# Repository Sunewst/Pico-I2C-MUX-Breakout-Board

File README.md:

<div align="center">

## Raspberry Pi Pico/W Breakout MUX Board

This PCB designed in KiCAD allows a Raspberry Pi Pico W, or normal version, to communicate with 8 I2C devices that have matching addresses. This board is based on breakout muiltiplexers sold by [Adafruit](https://www.adafruit.com/product/5626) and [SparkFun](https://www.sparkfun.com/sparkfun-qwiic-mux-breakout-8-channel-tca9548a.html). 

This also means the licence from these muiltiplexers, Creative Commons, applies to this one aswell.

</div>

---

## Arduino and CircuitPython
This breakout board works with either Arduino or CircuitPython.
> [!NOTE]
> For CircuitPython, I would recommend using the [libraries created by Adafruit for TCA9548a MUX use](https://learn.adafruit.com/adafruit-pca9548-8-channel-stemma-qt-qwiic-i2c-multiplexer/circuitpython-python).

The main connection are

SDA: GP4

SCL: GP5

MISO: GP16

MOSI: GP19

CLK: GP18

CS: GP17

Neopixel: GP6

---

## Creating and Changing this Design
1. Download the zip of this repo or clone it

2. Open the KiCAD project file.
> [!NOTE]
> This project was updated to KiCAD 9.0.

3. Examine and understand the schematic and PCB layout
> [!NOTE]
> The 3D models for the certain components might need to have their file path updated and their 3D models posistion adjusted to appear correctly on your PC.

4. Use your preferred PCB manufacture to order the PCB

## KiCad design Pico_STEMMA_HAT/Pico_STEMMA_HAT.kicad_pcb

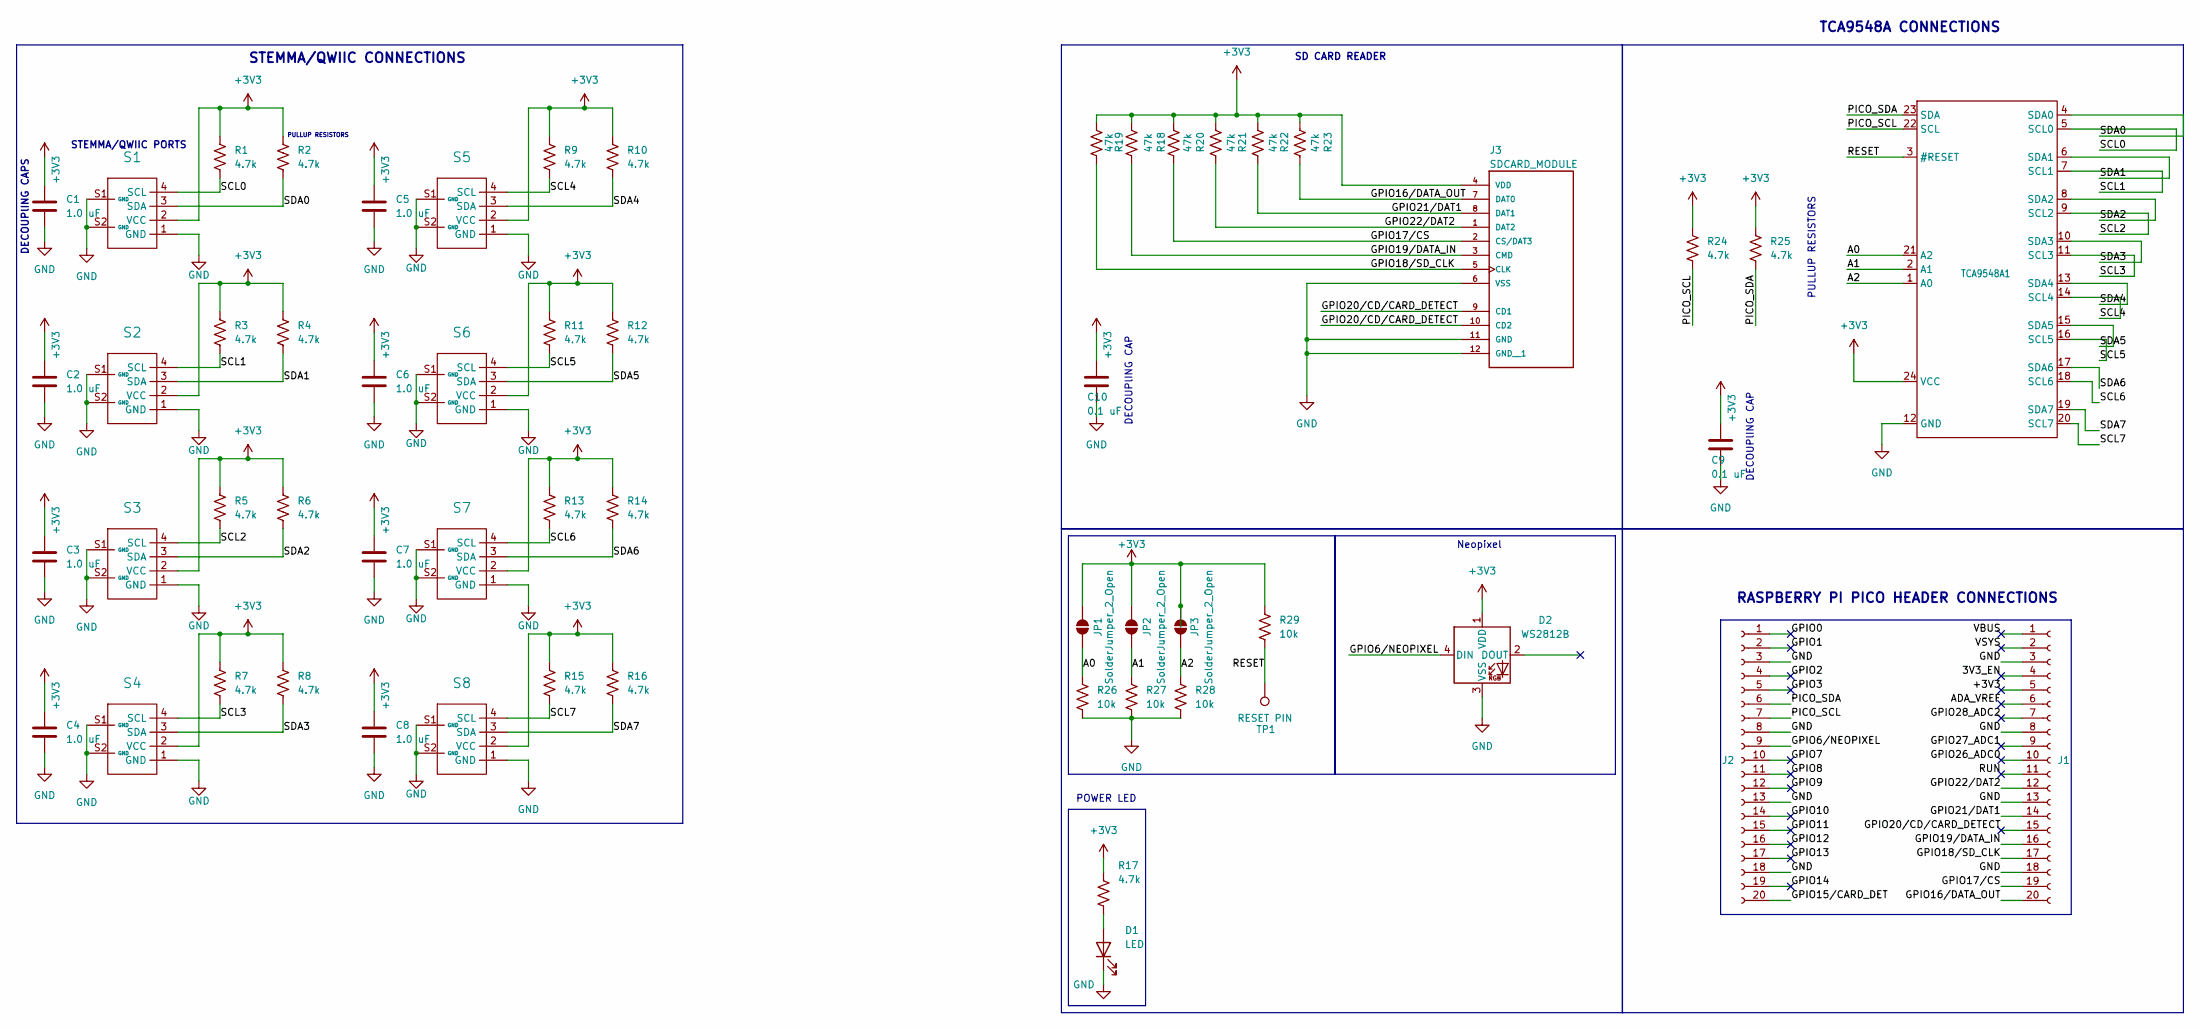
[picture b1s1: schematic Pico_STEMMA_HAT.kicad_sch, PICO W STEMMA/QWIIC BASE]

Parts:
C1, C2, C3, C4, C5, C6, C7, C8: 1.0 uF; C_0603_1608Metric
C9, C10: 0.1 uF; C_0603_1608Metric
D1: LED; LED_0603_1608Metric
D2: WS2812B; LED_WS2812B_PLCC4_5.0x5.0mm_P3.2mm
J1, J2: Conn_01x20_Socket; PinSocket_1x20_P2.54mm_Vertical
J3: SDCARD_MODULE; SDCARD_MODULE_Footprint
JP1, JP2, JP3: SolderJumper_2_Open; SolderJumper-2_P1.3mm_Open_TrianglePad1.0x1.5mm
R1, R2, R3, R4, R5, R6, R7, R8, R9, R10, R11, R12, R13, R14, R15, R16, R17, R24, R25: 4.7k; R_0603_1608Metric
R18, R19, R20, R21, R22, R23: 47k; R_0603_1608Metric
R26, R27, R28, R29: 10k; R_0603_1608Metric
S1, S2, S3, S4, S5, S6, S7, S8: STEMMAQWIIC_Footprint
TCA9548A1: TCA9548A_Footprint
TP1: RESET PIN; TestPoint_THTPad_1.0x1.0mm_Drill0.5mm

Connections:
+3V3: C1.1, C2.1, C3.1, C4.1, C5.1, C6.1, C7.1, C8.1, C9.1, C10.1, D2.1 (VDD), J1.5, J3.4 (VDD), JP1.2 (B), JP2.2 (B), JP3.2 (B), R1.1, R2.1, R3.1, R4.1, R5.1, R6.1, R7.1, R8.1, R9.1, R10.1, R11.1, R12.1, R13.1, R14.1, R15.1, R16.1, R17.1, R18.1, R19.1, R20.1, R21.1, R22.1, R23.1, R24.1, R25.1, R29.1, S1.2 (VCC), S2.2 (VCC), S3.2 (VCC), S4.2 (VCC), S5.2 (VCC), S6.2 (VCC), S7.2 (VCC), S8.2 (VCC), TCA9548A1.24 (VCC)
/3V3_EN: J1.4
/A0: JP1.1 (A), R26.1, TCA9548A1.21 (A2)
/A1: JP2.1 (A), R27.1, TCA9548A1.2 (A1)
/A2: JP3.1 (A), R28.1, TCA9548A1.1 (A0)
/ADA_VREF: J1.6
/GPIO0: J2.1
/GPIO1: J2.2
/GPIO2: J2.4
/GPIO3: J2.5
/GPIO6/NEOPIXEL: D2.4 (DIN), J2.9
/GPIO7: J2.10
/GPIO8: J2.11
/GPIO9: J2.12
/GPIO10: J2.14
/GPIO11: J2.15
/GPIO12: J2.16
/GPIO13: J2.17
/GPIO14: J2.19
/GPIO15/CARD_DET: J2.20
/GPIO16/DATA_OUT: J1.20, J3.7 (DAT0), R23.2
/GPIO17/CS: J1.19, J3.2 (CS/DAT3), R20.2
/GPIO18/SD_CLK: J1.17, J3.5 (CLK), R19.2
/GPIO19/DATA_IN: J1.16, J3.3 (CMD), R18.2
/GPIO20/CD/CARD_DETECT: J1.15, J3.9 (CD1), J3.10 (CD2)
/GPIO21/DAT1: J1.14, J3.8 (DAT1), R22.2
/GPIO22/DAT2: J1.12, J3.1 (DAT2), R21.2
/GPIO26_ADC0: J1.10
/GPIO27_ADC1: J1.9
/GPIO28_ADC2: J1.7
/PICO_SCL: J2.7, R24.2, TCA9548A1.22 (SCL)
/PICO_SDA: J2.6, R25.2, TCA9548A1.23 (SDA)
/RESET: R29.2, TCA9548A1.3 (#RESET), TP1.1
/RUN: J1.11
/SCL0: R1.2, S1.4 (SCL), TCA9548A1.5 (SCL0)
/SCL1: R3.2, S2.4 (SCL), TCA9548A1.7 (SCL1)
/SCL2: R5.2, S3.4 (SCL), TCA9548A1.9 (SCL2)
/SCL3: R7.2, S4.4 (SCL), TCA9548A1.11 (SCL3)
/SCL4: R9.2, S5.4 (SCL), TCA9548A1.14 (SCL4)
/SCL5: R11.2, S6.4 (SCL), TCA9548A1.16 (SCL5)
/SCL6: R13.2, S7.4 (SCL), TCA9548A1.18 (SCL6)
/SCL7: R15.2, S8.4 (SCL), TCA9548A1.20 (SCL7)
/SDA0: R2.2, S1.3 (SDA), TCA9548A1.4 (SDA0)
/SDA1: R4.2, S2.3 (SDA), TCA9548A1.6 (SDA1)
/SDA2: R6.2, S3.3 (SDA), TCA9548A1.8 (SDA2)
/SDA3: R8.2, S4.3 (SDA), TCA9548A1.10 (SDA3)
/SDA4: R10.2, S5.3 (SDA), TCA9548A1.13 (SDA4)
/SDA5: R12.2, S6.3 (SDA), TCA9548A1.15 (SDA5)
/SDA6: R14.2, S7.3 (SDA), TCA9548A1.17 (SDA6)
/SDA7: R16.2, S8.3 (SDA), TCA9548A1.19 (SDA7)
/VBUS: J1.1
/VSYS: J1.2
GND: C1.2, C2.2, C3.2, C4.2, C5.2, C6.2, C7.2, C8.2, C9.2, C10.2, D1.1 (K), D2.3 (VSS), J1.3, J1.8, J1.13, J1.18, J2.3, J2.8, J2.13, J2.18, J3.6 (VSS), J3.11 (GND), J3.12 (GND__1), R26.2, R27.2, R28.2, S1.1 (GND), S1.S1 (GND), S1.S2 (GND), S2.1 (GND), S2.S1 (GND), S2.S2 (GND), S3.1 (GND), S3.S1 (GND), S3.S2 (GND), S4.1 (GND), S4.S1 (GND), S4.S2 (GND), S5.1 (GND), S5.S1 (GND), S5.S2 (GND), S6.1 (GND), S6.S1 (GND), S6.S2 (GND), S7.1 (GND), S7.S1 (GND), S7.S2 (GND), S8.1 (GND), S8.S1 (GND), S8.S2 (GND), TCA9548A1.12 (GND)
unnamed: D1.2 (A), R17.2

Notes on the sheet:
STEMMA/QWIIC PORTS
SD CARD READER
RASPBERRY PI PICO HEADER CONNECTIONS
DECOUPlING CAP
TCA9548A CONNECTIONS
PULLUP RESISTORS
DECOUPlING CAPS
STEMMA/QWIIC CONNECTIONS
POWER LED
Neopixel

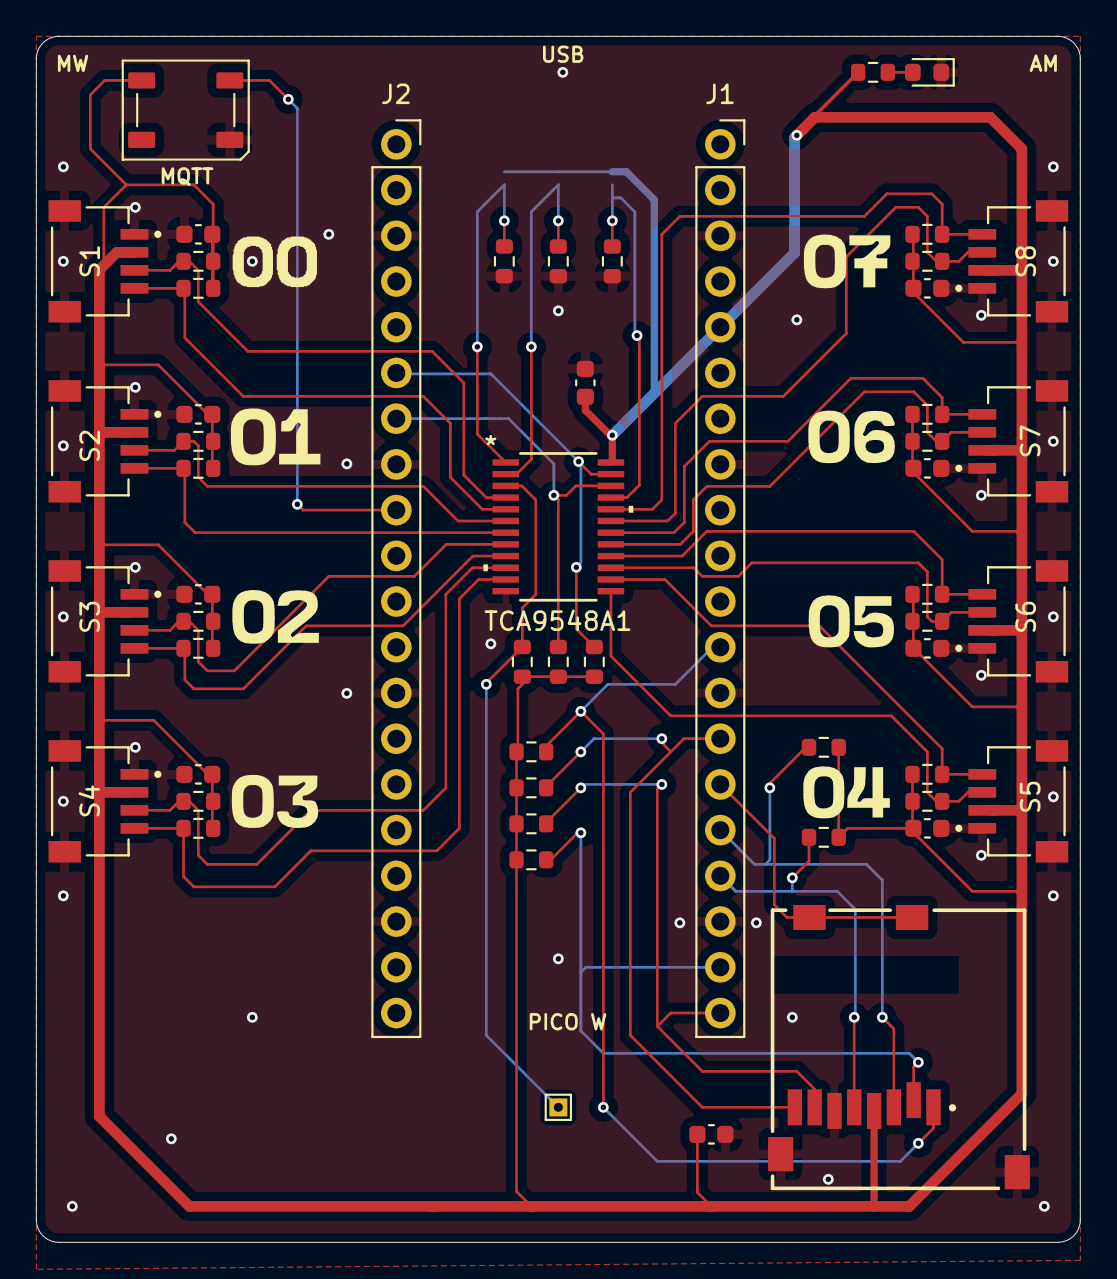
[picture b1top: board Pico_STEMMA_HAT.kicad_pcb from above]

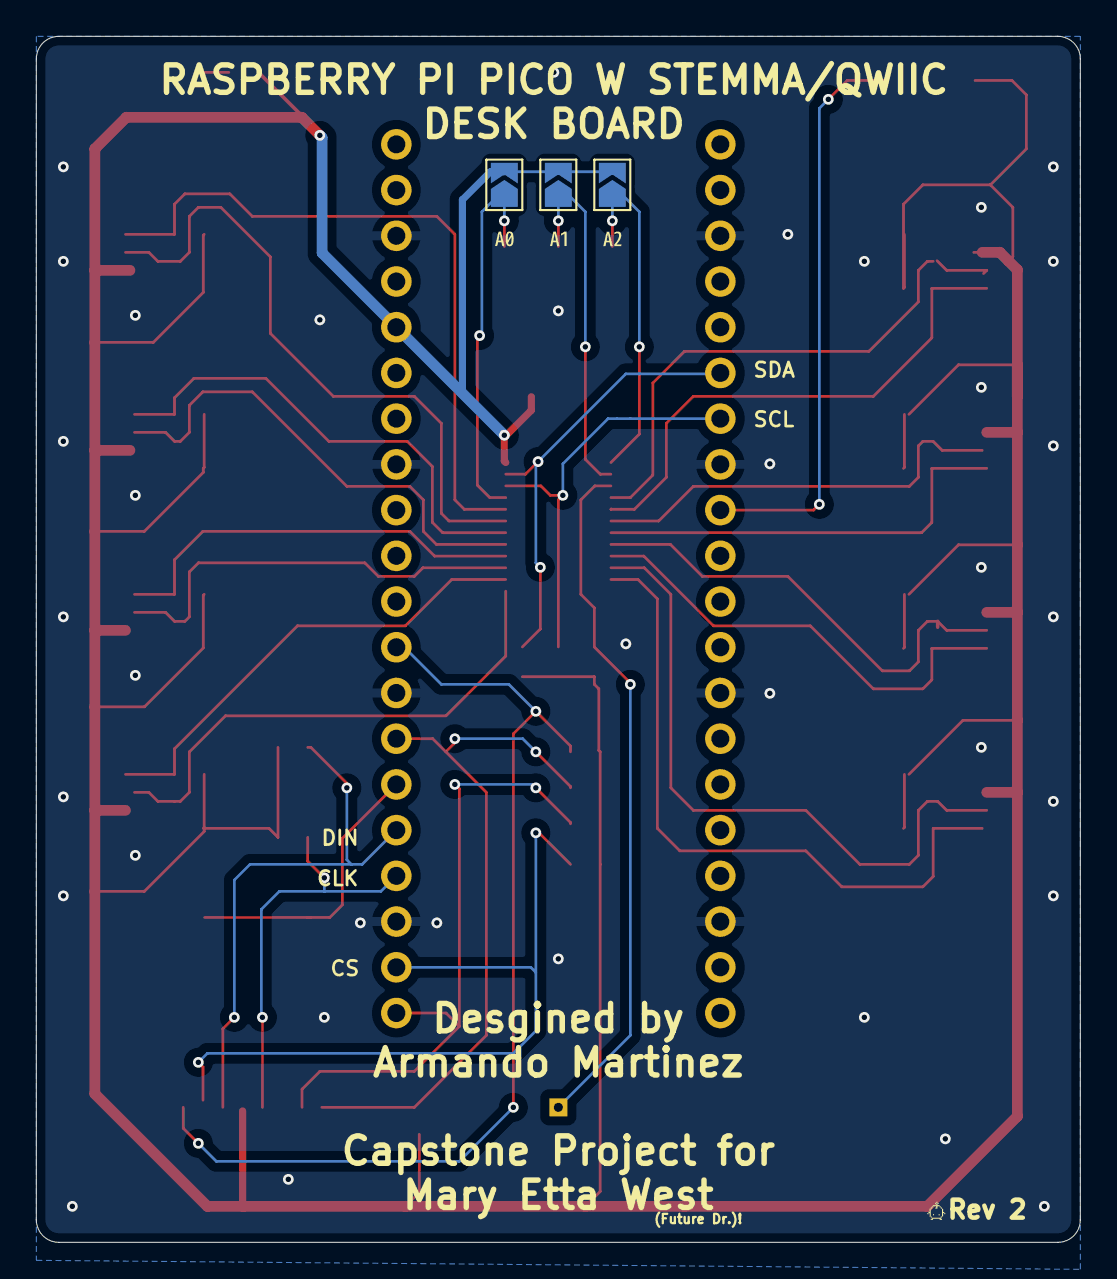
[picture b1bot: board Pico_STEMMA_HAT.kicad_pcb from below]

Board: 2 copper layers, 58.0 x 67.0 mm, 60 parts (6 on the bottom side), 33 nets.

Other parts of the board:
kibuzzard-67A6AC81: G***; kibuzzard-67A6AC81
kibuzzard-67A6B903: G***; kibuzzard-67A6B903
kibuzzard-67A6E024: G***; kibuzzard-67A6E024

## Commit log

2024-12-24 Update README.md to include the new project name
2025-01-05 Add Winter Break Progress
    Progress so far from learning KiCAD and creating the Pico W base over break. The SD card and coin battery will be added tomorrow when I create their footprints.
2025-01-05 Add STEMMA connector pads to the GND net
2025-01-05 Add 3D models for STEMMA connectors and TCA9548A
2025-01-06 Fix errors from the DRC
    The design rules are based around the JLCPCB manufacturer
2025-01-06 Rearranged traces
2025-01-06 Reroute traces
2025-01-08 Add 3D models to the repo
2025-01-09 Add SD Card symbol and footprint
2025-01-09 Fix 3D model rendering in MacOS
2025-01-11 Add GND vias to connect STEMMA GNDs
2025-01-11 Add GND vias to connect to GND B layer
2025-01-15 Add SD Card reader to schem
2025-01-15 Add SD card reader to PCB design
2025-01-15 Add pullup resistors to the SD card reader
2025-01-15 Adjust traces
2025-01-16 Change pullup resistors
2025-01-16 Add 3D models for SD card and Neopixel
2025-01-16 Fix STEMMA GND Nets
2025-01-16 Add temp project logo
2025-01-16 Remove concept logo
2025-01-16 Add PNG of the 3D model of the board
2025-01-16 Fix SD Card connections
2025-01-16 Fix MacOS 3D models
2025-01-18 Adjust traces according to oshpark DRC
2025-01-21 Add STEMMA numbers and credits
2025-01-21 Adjust silkscreen
2025-01-21 Fix fonts
2025-01-22 Add decoupling cap for the SD card reader
2025-01-23 Add Gameboy Color ref
2025-02-07 Fix pull-up resistors for multiplexer
    Add the pull-up resistors from the schem to the PCB design. Adjusted resistor value for red LED. Adjusted Neopixel footprint.
2025-02-07 Change 3D model preview image
2025-02-07 Change page settings
2025-02-07 Fix Neopixel footprint
2025-02-07 Adjust through-hole connectors
2025-02-08 Add the ability to change multiplexer address
2025-02-08 Adjust SD card pin for OCD-reasons
2025-02-08 Fix pin name
2025-02-08 Adjust sch layout
2025-02-08 Change reset pin to be out in the open
2025-02-08 Adjust reset pin trace
2025-02-08 Add oshpark order front and back side PCB view
2025-02-10 Add silkscreen appreciation
2025-03-04 Update schematic formatting
2025-03-04 Update schematic
2025-03-28 Adjust vias
2025-03-31 Adjust repo for public release
